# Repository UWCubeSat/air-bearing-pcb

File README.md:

# [PCB for the Air Bearing](https://online.huskysatellitelab.com/wiki/index.php/2021_Intro_Projects#Design_PCB_for_the_Air_Bearing)

As the project developed over the course of the summer, our air bearing test stand's electrical system needed to be quickly assembled onto a perfboard Arduino shield. Now that we have time, we'd like to replace that janky jury-rigged board with a PCB to make the system more robust and reduce the number of loose wires holding the electronics together. Currently, the circuit is responsible for connecting the I2C lines of the Arduino Uno to several sensors and an external system through a logic level shifter, communicating with a Bluetooth module over UART, receiving power from a battery, and providing reset functionality in software.

**Point of Contact:** Sebastian Soetomo or Andrew Buckingham

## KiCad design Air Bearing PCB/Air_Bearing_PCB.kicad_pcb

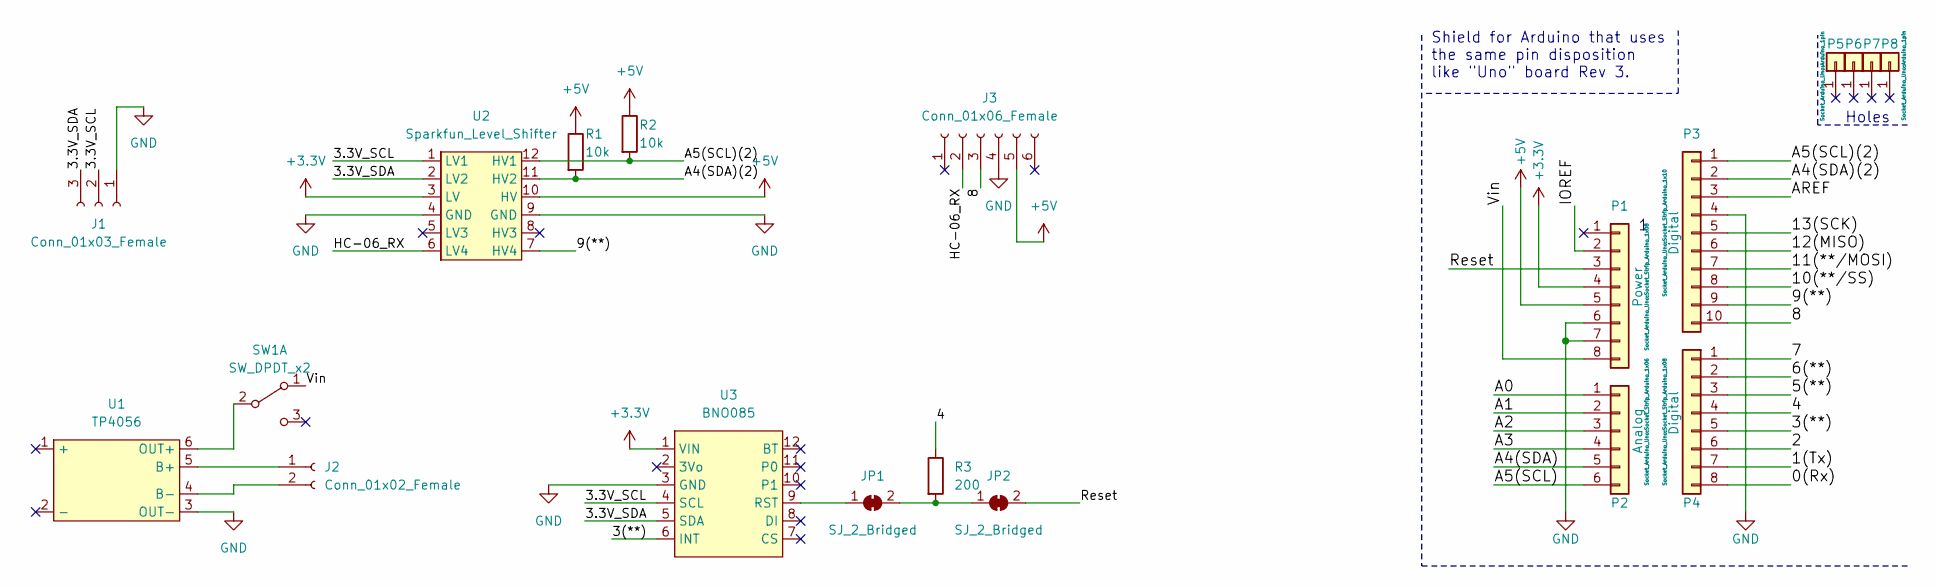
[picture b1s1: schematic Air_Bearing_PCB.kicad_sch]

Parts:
J1: Conn_01x03_Female; PinSocket_1x03_P2.54mm_Vertical
J2: Conn_01x02_Female; PinSocket_1x02_P2.54mm_Vertical
J3: Conn_01x06_Female; PinSocket_1x06_P2.54mm_Vertical
JP1, JP2: SJ_2_Bridged; SolderJumper-2_P1.3mm_Open_RoundedPad1.0x1.5mm
P1: Power; Socket_Strip_Arduino_1x08
P2: Analog; Socket_Strip_Arduino_1x06
P3: Digital; Socket_Strip_Arduino_1x10
P4: Digital; Socket_Strip_Arduino_1x08
P5, P6, P7, P8: CONN_01X01; Arduino_1pin
R1, R2: 10k; R_0603_1608Metric_Pad0.98x0.95mm_HandSolder
R3: 200; R_0603_1608Metric_Pad0.98x0.95mm_HandSolder
SW1: SW_DPDT_x2; PinHeader_1x03_P2.54mm_Vertical
U1: TP4056
U2: Sparkfun_Level_Shifter; Level_Shifter
U3: BNO085

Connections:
+3V3: P1.4, U2.3 (LV), U3.1 (VIN)
+5V: J3.5, P1.5, R1.1, R2.1, U2.10 (HV)
/0(Rx): P4.8
/1(Tx): P4.7
/2: P4.6
/3(**): P4.5, U3.6 (INT)
/3.3V_SCL: J1.2, U2.1 (LV1), U3.4 (SCL)
/3.3V_SDA: J1.3, U2.2 (LV2), U3.5 (SDA)
/4: P4.4, R3.1
/5(**): P4.3
/6(**): P4.2
/7: P4.1
/8: J3.3, P3.10
/9(**): P3.9, U2.7 (HV4)
/10(**/SS): P3.8
/11(**/MOSI): P3.7
/12(MISO): P3.6
/13(SCK): P3.5
/A0: P2.1
/A1: P2.2
/A2: P2.3
/A3: P2.4
/A4(SDA): P2.5
/A4(SDA)(2): P3.2, R1.2, U2.11 (HV2)
/A5(SCL): P2.6
/A5(SCL)(2): P3.1, R2.2, U2.12 (HV1)
/AREF: P3.3
/HC-06_RX: J3.2, U2.6 (LV4)
/IOREF: P1.2
/Reset: JP2.2 (B), P1.3
/Vin: P1.8, SW1.1 (A)
GND: J1.1, J3.4, P1.6, P1.7, P3.4, U1.3 (OUT-), U2.4 (GND), U2.9 (GND), U3.3 (GND)
unnamed: J2.1, U1.5 (B+)
unnamed: J2.2, U1.4 (B-)
unnamed: JP1.1 (A), U3.9 (RST)
unnamed: JP1.2 (B), JP2.1 (A), R3.2
unnamed: SW1.2 (B), U1.6 (OUT+)

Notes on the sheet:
Holes
Shield for Arduino that uses the same pin disposition like "Uno" board Rev 3.

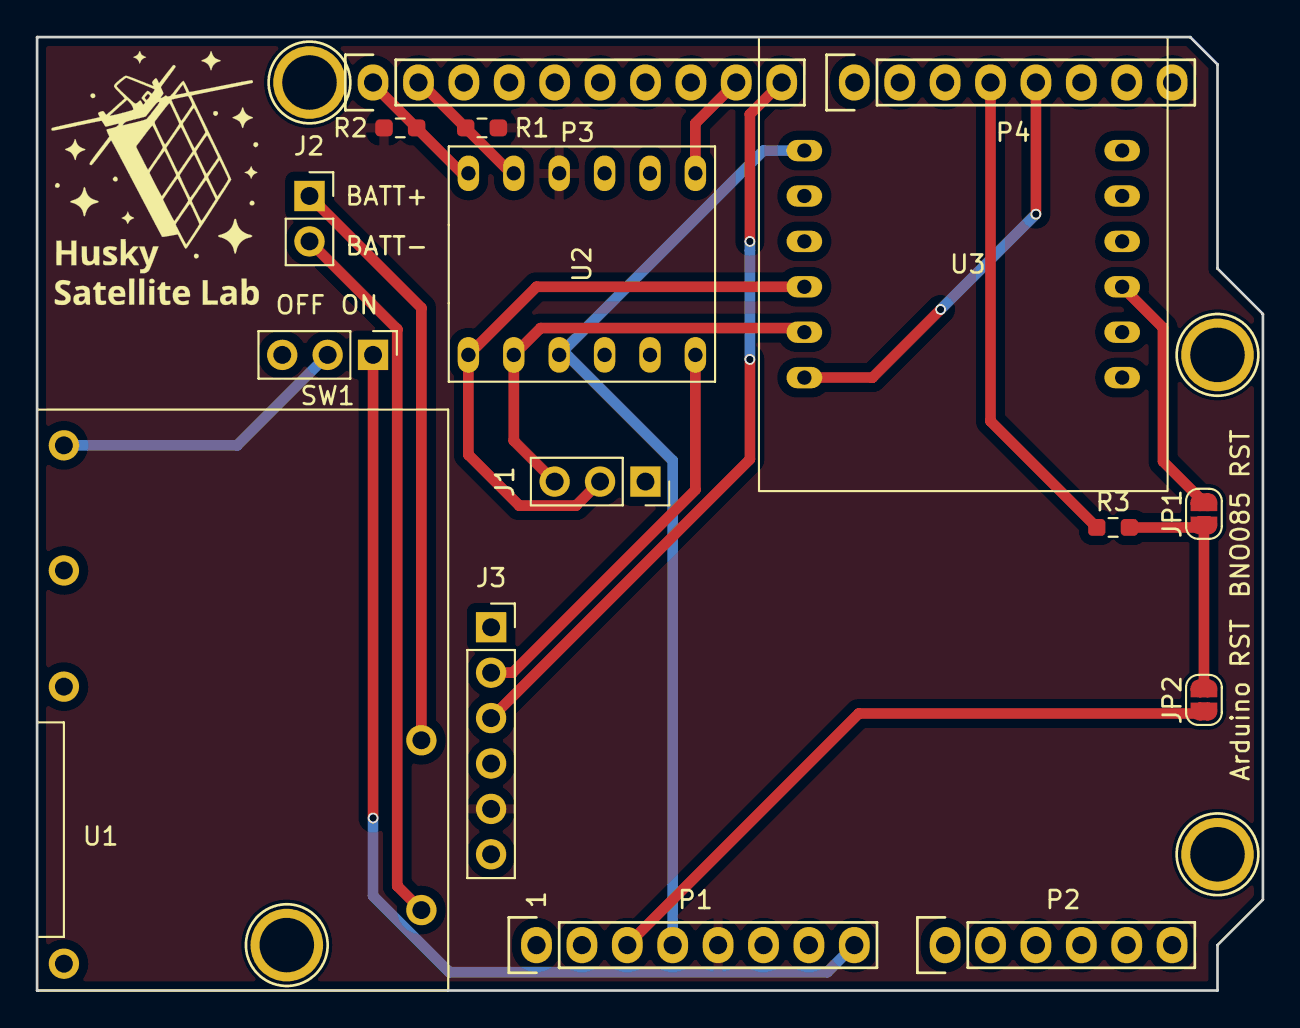
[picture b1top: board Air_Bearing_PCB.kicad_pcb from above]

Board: 2 copper layers, 68.6 x 53.3 mm, 20 parts (0 on the bottom side), 19 nets.

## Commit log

2021-10-22 Updated README.md
    Copied description and link from wiki
2022-02-14 Added preliminary PCB
    Added preliminary PCB and updated README
2022-02-15 Added Gerber Files
    Made a few small routing and schematic edits. Added Gerber files.
